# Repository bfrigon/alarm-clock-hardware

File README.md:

alarm-clock
===========

Project page at http://www.bfrigon.com/posts/projects/alarm-clock

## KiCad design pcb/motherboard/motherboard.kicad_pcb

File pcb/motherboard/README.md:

### Motherboard ###

```
Part #  : CLK-PC-03
REV.    : A
```

#### Documents ####

* [Schematic (PDF)](https://raw.githubusercontent.com/bfrigon/project-alarm-clock/master/drawings/schematics/clk-sch-03.pdf)
* [Bill of material](/pcb/motherboard/bom/bom.md)

#### 3D render ####

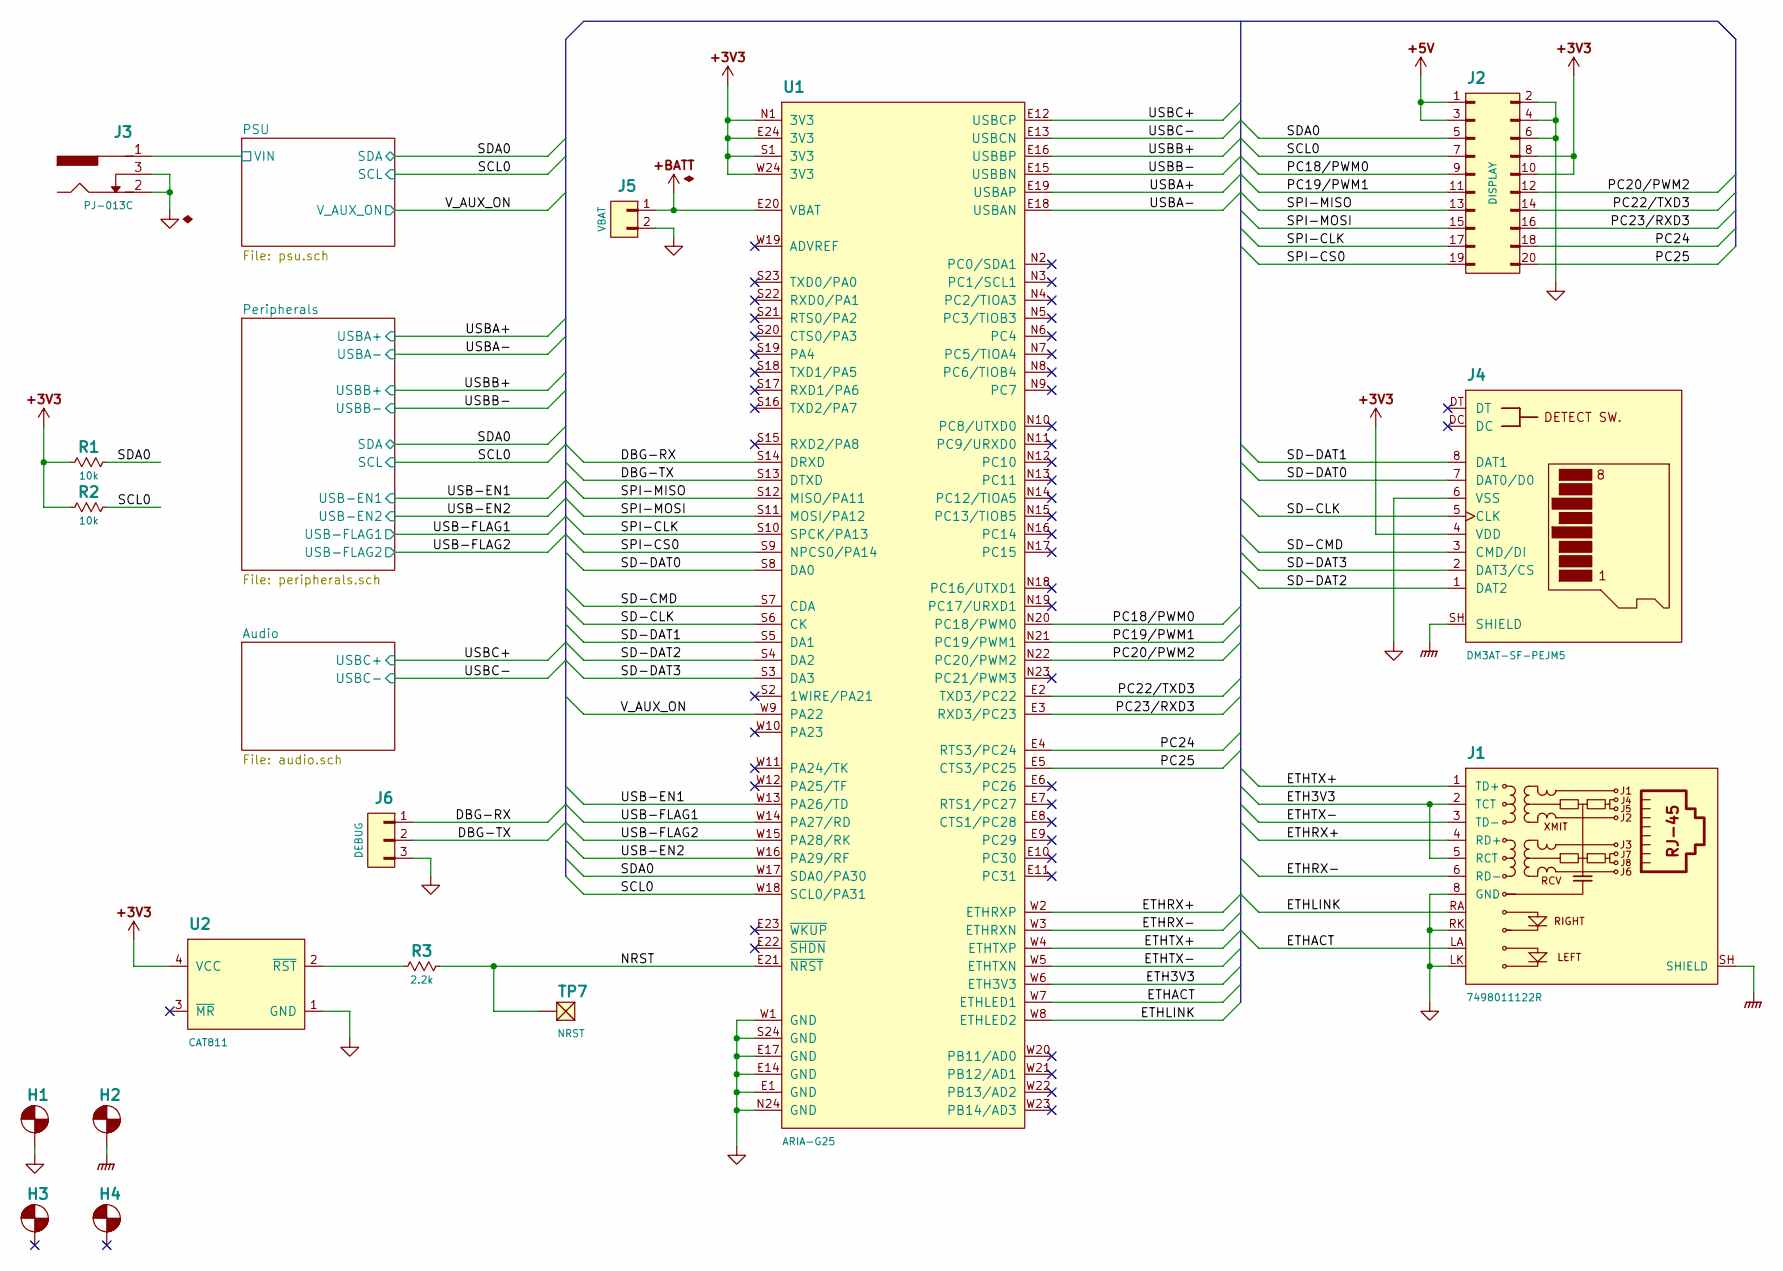
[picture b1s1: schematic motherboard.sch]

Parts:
H1, H2, H3, H4: Hole; Hole-Screw-#4
J1: 7498011122R; RJ45-WURTH-7498011122R
J2: DISPLAY; DF13A-20DP-1.25
J3: PJ-013C; CUI-PJ-031CH
J4: DM3AT-SF-PEJM5; HIROSE-MICROSD-DM3AT-SF
J5: VBAT; WP-75mil-1x02
J6: DEBUG; DF3DZ-3P-2VXX
R1, R2: 10k; R-0603
R3: 2.2k; R-0603
TP7: NRST; TEST-POINT-50
U1: ARIA-G25
U2: CAT811; SOT-143

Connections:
+BATT: J5.1, U1.E20 (VBAT)
/Audio/USBC+: U1.E12 (USBCP); also elsewhere on the board
/Audio/USBC-: U1.E13 (USBCN); also elsewhere on the board
/DBG-RX: J6.1, U1.S14 (DRXD)
/DBG-TX: J6.2, U1.S13 (DTXD)
/ETH3V3: J1.2 (TCT), J1.5 (RCT), U1.W6 (ETH3V3)
/ETHACT: J1.LA, U1.W7 (ETHLED1)
/ETHLINK: J1.RA, U1.W8 (ETHLED2)
/ETHRX+: J1.4 (RD+), U1.W2 (ETHRXP)
/ETHRX-: J1.6 (RD-), U1.W3 (ETHRXN)
/ETHTX+: J1.1 (TD+), U1.W4 (ETHTXP)
/ETHTX-: J1.3 (TD-), U1.W5 (ETHTXN)
/NRST: R3.2, TP7.1, U1.E21 (~NRST)
/PC18/PWM0: J2.9, U1.N20 (PC18/PWM0)
/PC19/PWM1: J2.11, U1.N21 (PC19/PWM1)
/PC20/PWM2: J2.12, U1.N22 (PC20/PWM2)
/PC22/TXD3: J2.14, U1.E2 (TXD3/PC22)
/PC23/RXD3: J2.16, U1.E3 (RXD3/PC23)
/PC24: J2.18, U1.E4 (RTS3/PC24)
/PC25: J2.20, U1.E5 (CTS3/PC25)
/PSU/SCL: J2.7, R2.2, U1.W18 (SCL0/PA31); also elsewhere on the board
/PSU/SDA: J2.5, R1.2, U1.W17 (SDA0/PA30); also elsewhere on the board
/PSU/VIN: J3.1; also elsewhere on the board
/PSU/V_AUX_ON: U1.W9 (PA22); also elsewhere on the board
/Peripherals/USB-EN1: U1.W13 (PA26/TD); also elsewhere on the board
/Peripherals/USB-EN2: U1.W16 (PA29/RF); also elsewhere on the board
/Peripherals/USB-FLAG1: U1.W14 (PA27/RD); also elsewhere on the board
/Peripherals/USB-FLAG2: U1.W15 (PA28/RK); also elsewhere on the board
/Peripherals/USBA+: U1.E19 (USBAP); also elsewhere on the board
/Peripherals/USBA-: U1.E18 (USBAN); also elsewhere on the board
/Peripherals/USBB+: U1.E16 (USBBP); also elsewhere on the board
/Peripherals/USBB-: U1.E15 (USBBN); also elsewhere on the board
/SD-CLK: J4.5 (CLK), U1.S6 (CK)
/SD-CMD: J4.3 (CMD/DI), U1.S7 (CDA)
/SD-DAT0: J4.7 (DAT0/D0), U1.S8 (DA0)
/SD-DAT1: J4.8 (DAT1), U1.S5 (DA1)
/SD-DAT2: J4.1 (DAT2), U1.S4 (DA2)
/SD-DAT3: J4.2 (DAT3/CS), U1.S3 (DA3)
/SPI-CLK: J2.17, U1.S10 (SPCK/PA13)
/SPI-CS0: J2.19, U1.S9 (NPCS0/PA14)
/SPI-MISO: J2.13, U1.S12 (MISO/PA11)
/SPI-MOSI: J2.15, U1.S11 (MOSI/PA12)
unnamed: R3.1, U2.2 (~RST)

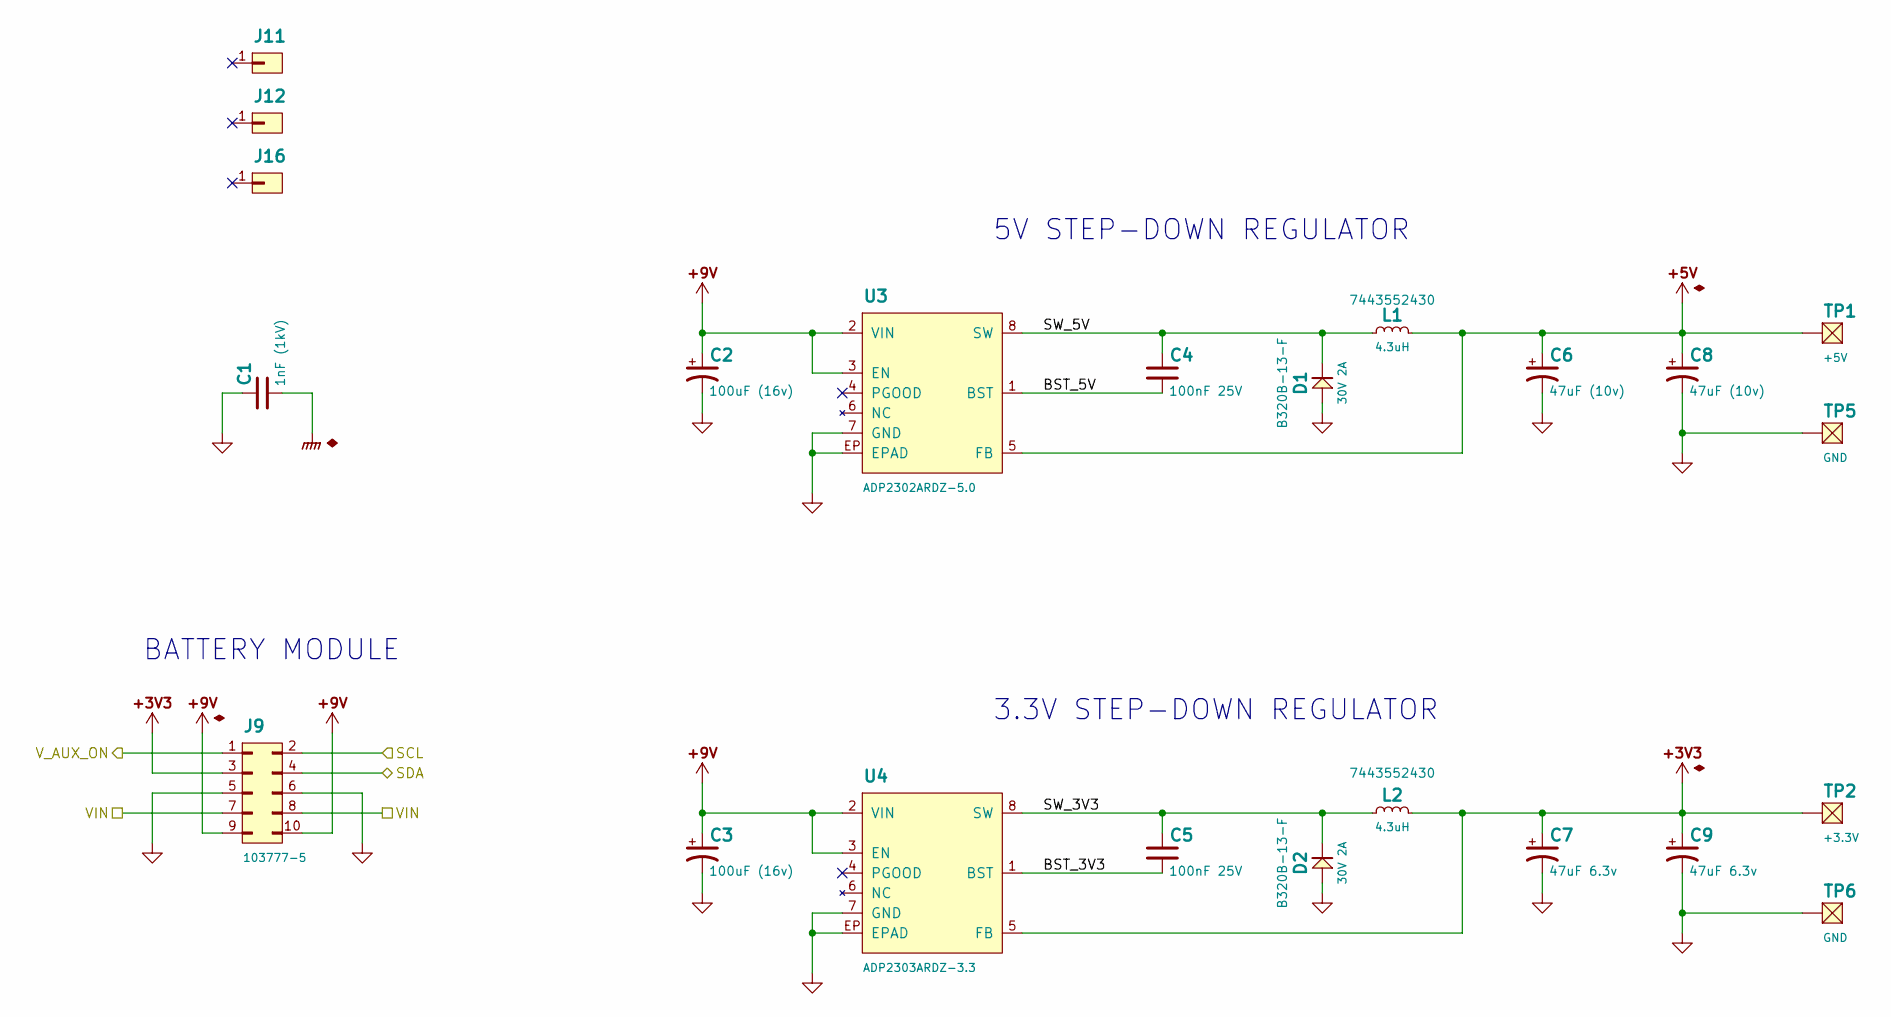
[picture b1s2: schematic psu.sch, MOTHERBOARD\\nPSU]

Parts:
C1: 1nF (1kV); C-0805
C2, C3: 100uF (16v); CPL-1210; Part EMK325ABJ107MM-T
C4, C5: 100nF 25V; C-0603
C6, C8: 47uF (10v); CPL-1206; Part LMK316BJ476ML-T
C7: 47uF 6.3v; CPL-1206; Part GRM31CR60J476ME19K
C9: 47uF 6.3v; CPL-1206; Part# GRM31CR60J476ME19K
D1: 30V 2A; DO-214-AA; PART B320B-13-F
D2: 30V 2A; DO-214-AA; Part B320B-13-F
J9: 103777-5; HDR-M-2x05
J11, J12, J16: 103741-1; HDR-M-1x01
L1, L2: 4.3uH; IND-10X10; PART 7443552430
TP1: +5V; TEST-POINT-50
TP2: +3.3V; TEST-POINT-50
TP5, TP6: GND; TEST-POINT-50
U3: ADP2302ARDZ-5.0; 8-EP
U4: ADP2303ARDZ-3.3; 8-EP

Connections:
/PSU/BST_3V3: C5.1, U4.1 (BST)
/PSU/BST_5V: C4.1, U3.1 (BST)
/PSU/SCL: J9.2; also elsewhere on the board
/PSU/SDA: J9.4; also elsewhere on the board
/PSU/SW_3V3: C5.2, D2.K, L2.1, U4.8 (SW)
/PSU/SW_5V: C4.2, D1.K, L1.1, U3.8 (SW)
/PSU/VIN: J9.7, J9.8; also elsewhere on the board
/PSU/V_AUX_ON: J9.1; also elsewhere on the board

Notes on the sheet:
5V STEP-DOWN REGULATOR
3.3V STEP-DOWN REGULATOR
BATTERY MODULE

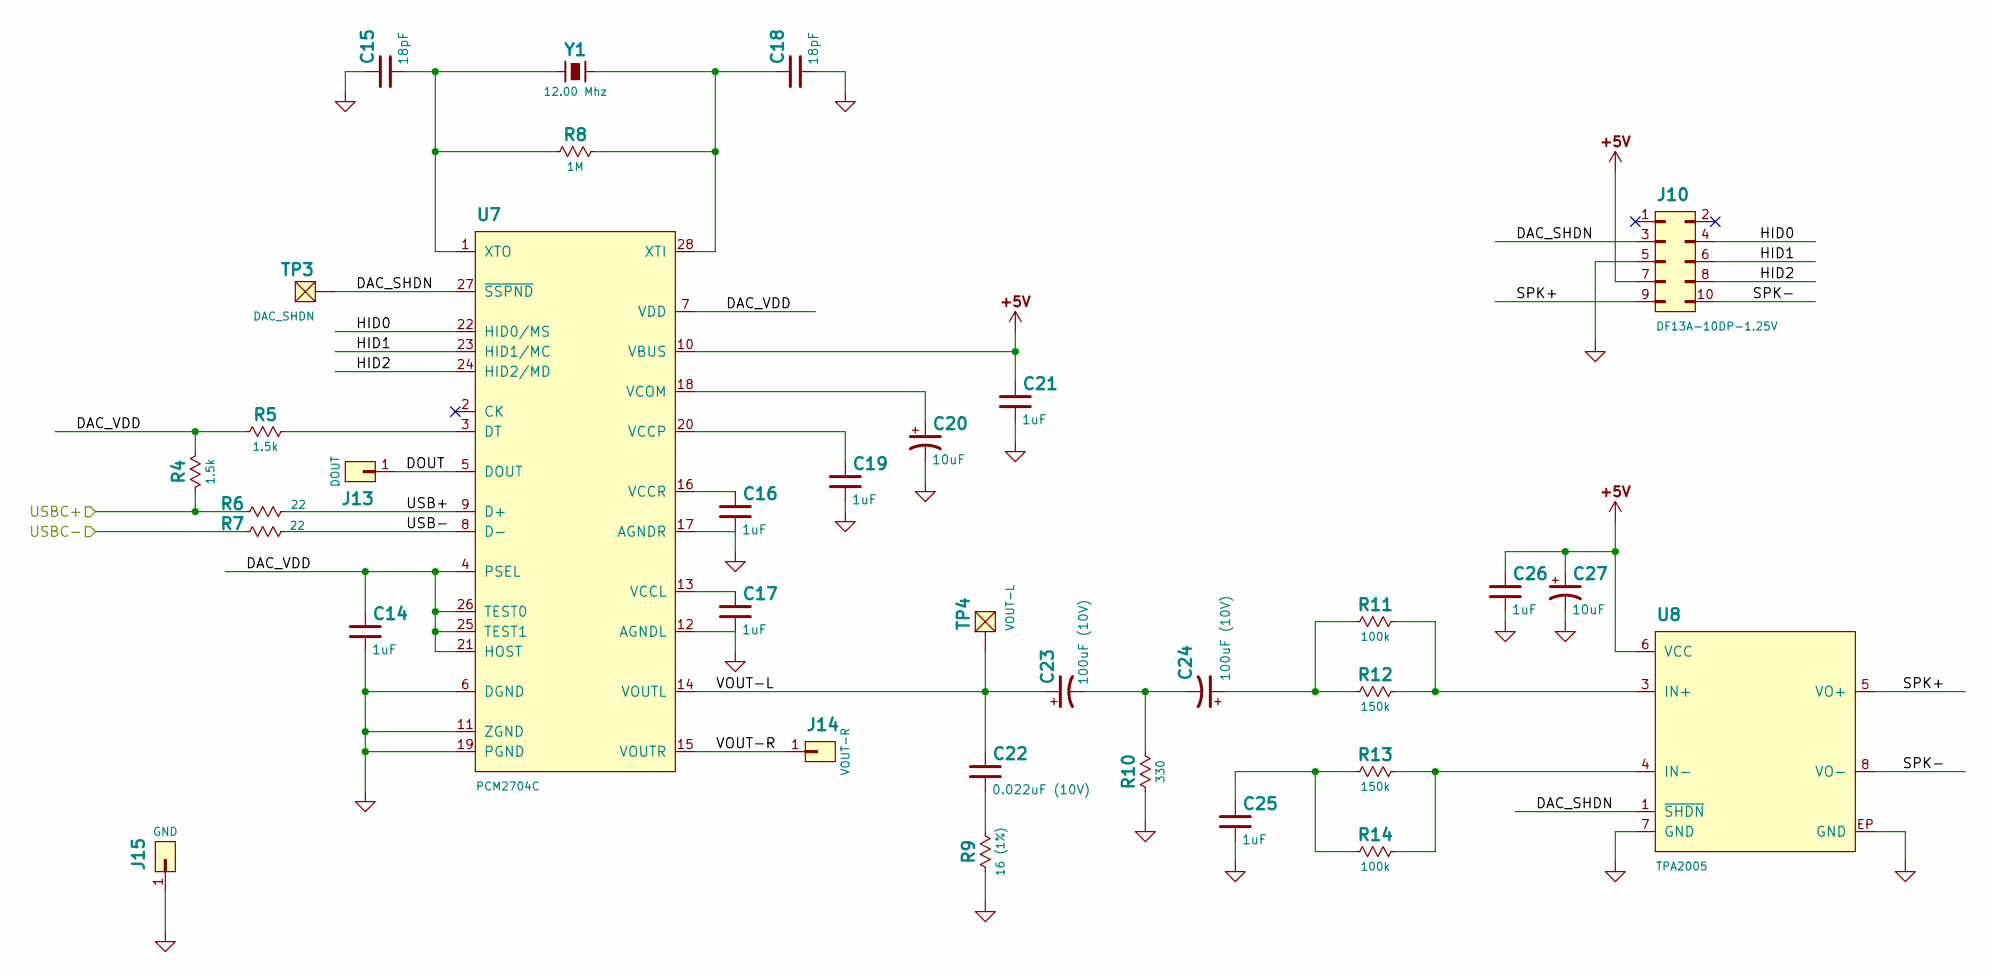
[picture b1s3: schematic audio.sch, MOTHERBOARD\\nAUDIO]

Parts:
C14, C16, C17, C19, C21, C25, C26: 1uF; C-0603
C15, C18: 18pF; C-0603
C20, C27: 10uF; CPL-0805
C22: 0.022uF (10V); C-0603
C23: 100uF (10V); CPL-1210
C24: 100uF (10V); CPL-0805
J10: DF13A-10DP-1.25V; DF13A-10DP-1.25
J13: DOUT; WP-50mil-1x01
J14: VOUT-R; WP-50mil-1x01
J15: GND; WP-50mil-1x01
R4, R5: 1.5k; R-0603
R6, R7: 22; R-0603
R8: 1M; R-0603
R9: 16 (1%); R-0603
R10: 330; R-0603
R11, R14: 100k; R-0603
R12, R13: 150k; R-0603
TP3: DAC_SHDN; TEST-POINT-50
TP4: VOUT-L; TEST-POINT-50
U7: PCM2704C; SSOP28
U8: TPA2005; PPSOP8
Y1: 12.00 Mhz; HC49UP

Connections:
/Audio/DAC_SHDN: J10.3, TP3.1, U7.27 (~SSPND), U8.1 (~SHDN)
/Audio/DAC_VDD: C14.2, R4.1, R5.1, U7.4 (PSEL), U7.7 (VDD), U7.21 (HOST), U7.25 (TEST1), U7.26 (TEST0)
/Audio/DOUT: J13.1, U7.5 (DOUT)
/Audio/HID0: J10.4, U7.22 (HID0/MS)
/Audio/HID1: J10.6, U7.23 (HID1/MC)
/Audio/HID2: J10.8, U7.24 (HID2/MD)
/Audio/SPK+: J10.9, U8.5 (VO+)
/Audio/SPK-: J10.10, U8.8 (VO-)
/Audio/USB+: R6.2, U7.9 (D+)
/Audio/USB-: R7.2, U7.8 (D-)
/Audio/USBC+: R4.2, R6.1; also elsewhere on the board
/Audio/USBC-: R7.1; also elsewhere on the board
/Audio/VOUT-L: C22.2, C23.A, TP4.1, U7.14 (VOUTL)
/Audio/VOUT-R: J14.1, U7.15 (VOUTR)
unnamed: C15.1, R8.1, U7.1 (XTO), Y1.1
unnamed: C16.2, U7.16 (VCCR)
unnamed: C17.2, U7.13 (VCCL)
unnamed: C18.2, R8.2, U7.28 (XTI), Y1.2
unnamed: C19.2, U7.20 (VCCP)
unnamed: C20.A, U7.18 (VCOM)
unnamed: C22.1, R9.2
unnamed: C23.K, C24.K, R10.2
unnamed: C24.A, R11.1, R12.1
unnamed: C25.2, R13.1, R14.1
unnamed: R5.2, U7.3 (DT)
unnamed: R11.2, R12.2, U8.3 (IN+)
unnamed: R13.2, R14.2, U8.4 (IN-)

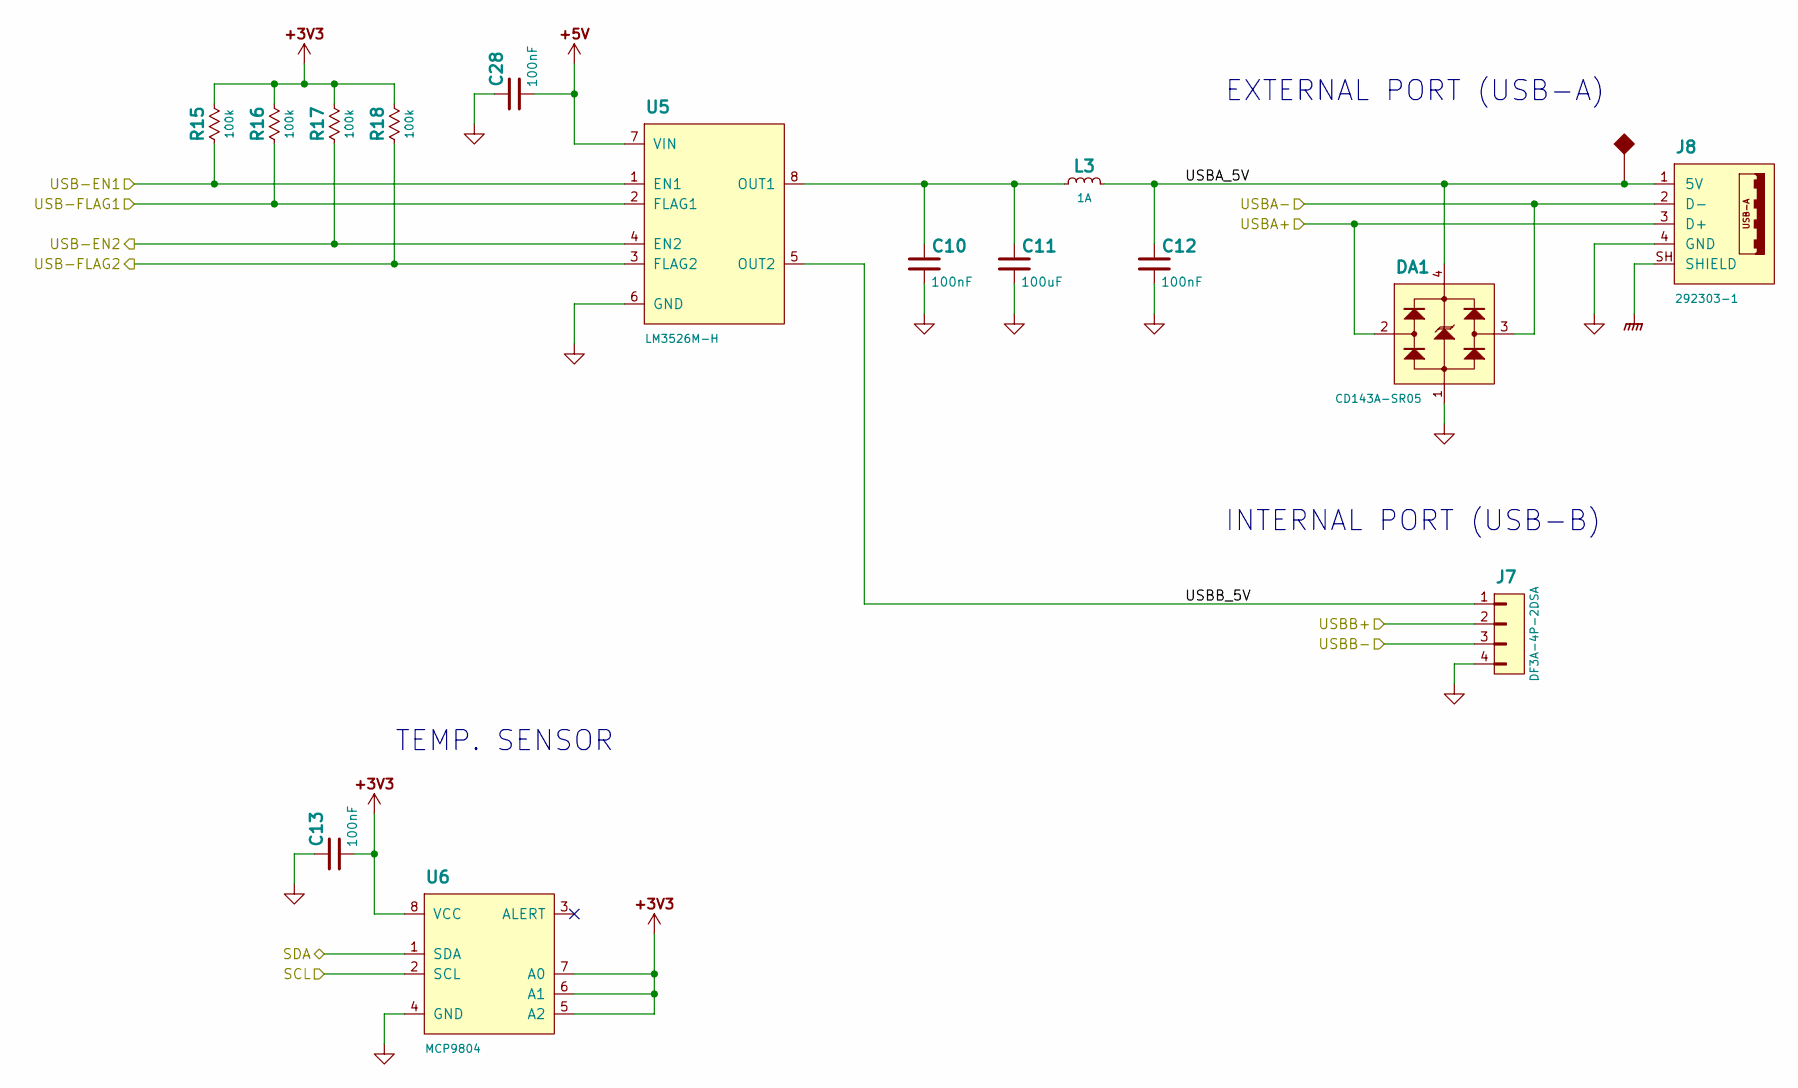
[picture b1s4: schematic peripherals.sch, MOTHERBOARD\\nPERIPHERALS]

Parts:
C10, C12, C13, C28: 100nF; C-0603
C11: 100uF; C-0805
DA1: CD143A-SR05; SOT-143
J7: DF3A-4P-2DSA
J8: 292303-1; USBA-TE-292303-1
L3: 1A; FER-0805
R15, R16, R17, R18: 100k; R-0603
U5: LM3526M-H; 8
U6: MCP9804; MSOP8

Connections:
/PSU/SCL: U6.2 (SCL); also elsewhere on the board
/PSU/SDA: U6.1 (SDA); also elsewhere on the board
/Peripherals/USB-EN1: R15.1, U5.1 (EN1); also elsewhere on the board
/Peripherals/USB-EN2: R17.1, U5.4 (EN2); also elsewhere on the board
/Peripherals/USB-FLAG1: R16.1, U5.2 (FLAG1); also elsewhere on the board
/Peripherals/USB-FLAG2: R18.1, U5.3 (FLAG2); also elsewhere on the board
/Peripherals/USBA+: DA1.2, J8.3 (D+); also elsewhere on the board
/Peripherals/USBA-: DA1.3, J8.2 (D-); also elsewhere on the board
/Peripherals/USBA_5V: C12.2, DA1.4, J8.1 (5V), L3.2
/Peripherals/USBB+: J7.2; also elsewhere on the board
/Peripherals/USBB-: J7.3; also elsewhere on the board
/Peripherals/USBB_5V: J7.1, U5.5 (OUT2)
unnamed: C10.2, C11.2, L3.1, U5.8 (OUT1)

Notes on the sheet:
INTERNAL PORT (USB-B)
EXTERNAL PORT (USB-A)
TEMP. SENSOR

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
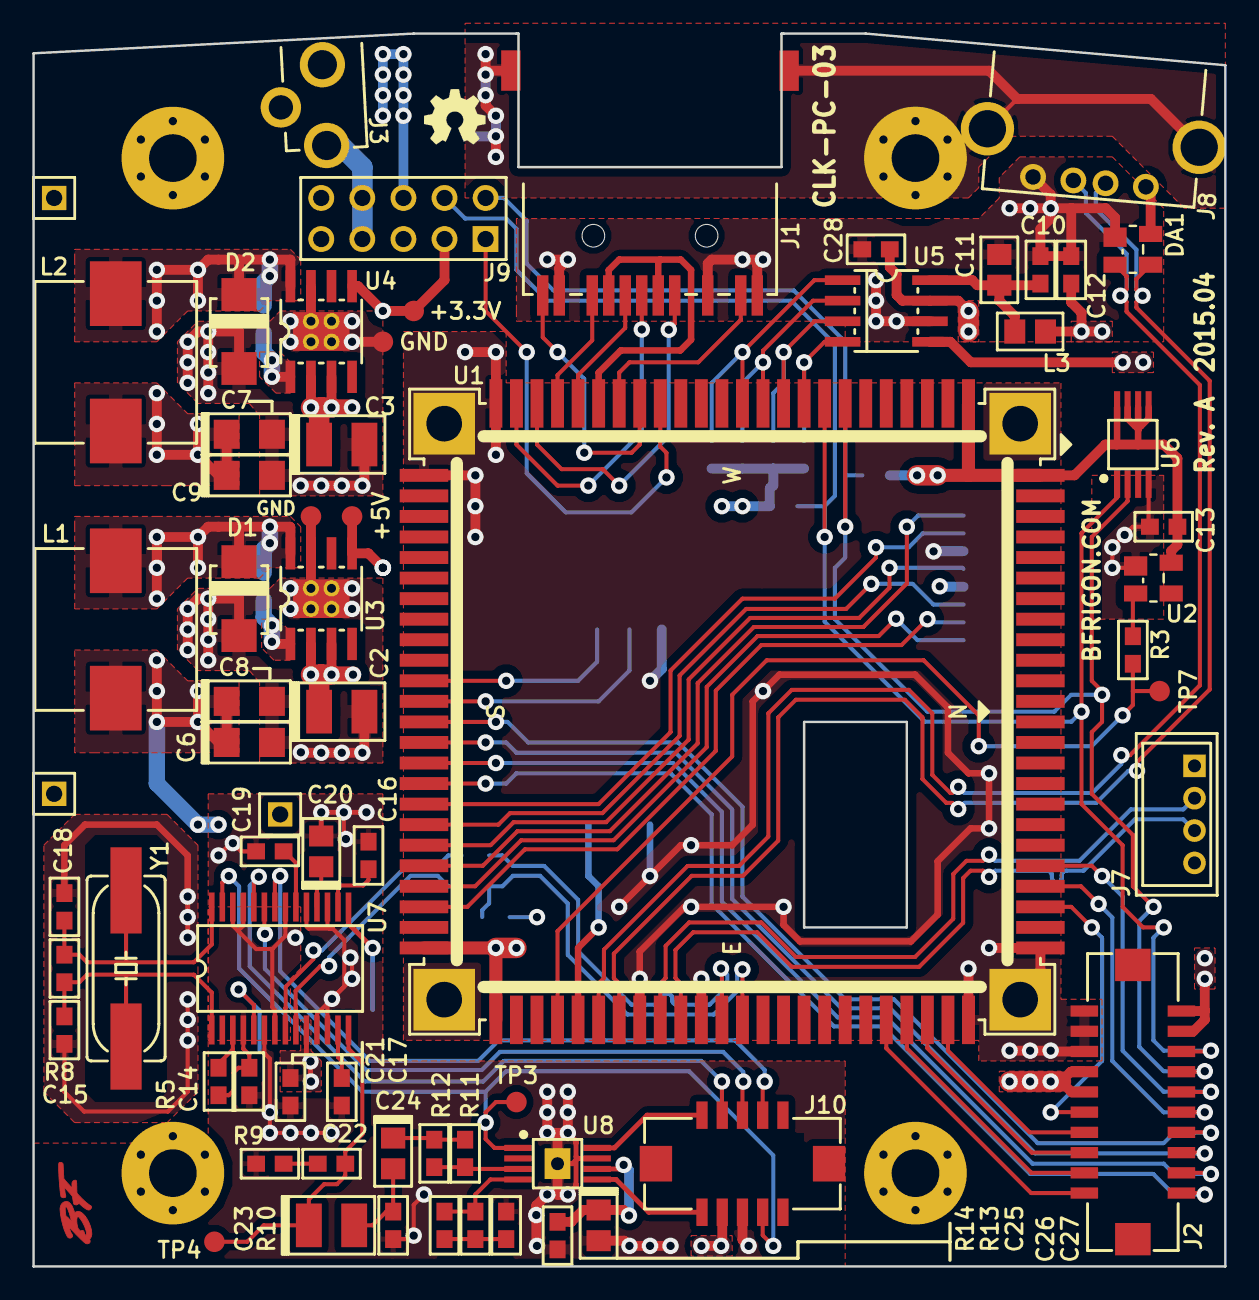
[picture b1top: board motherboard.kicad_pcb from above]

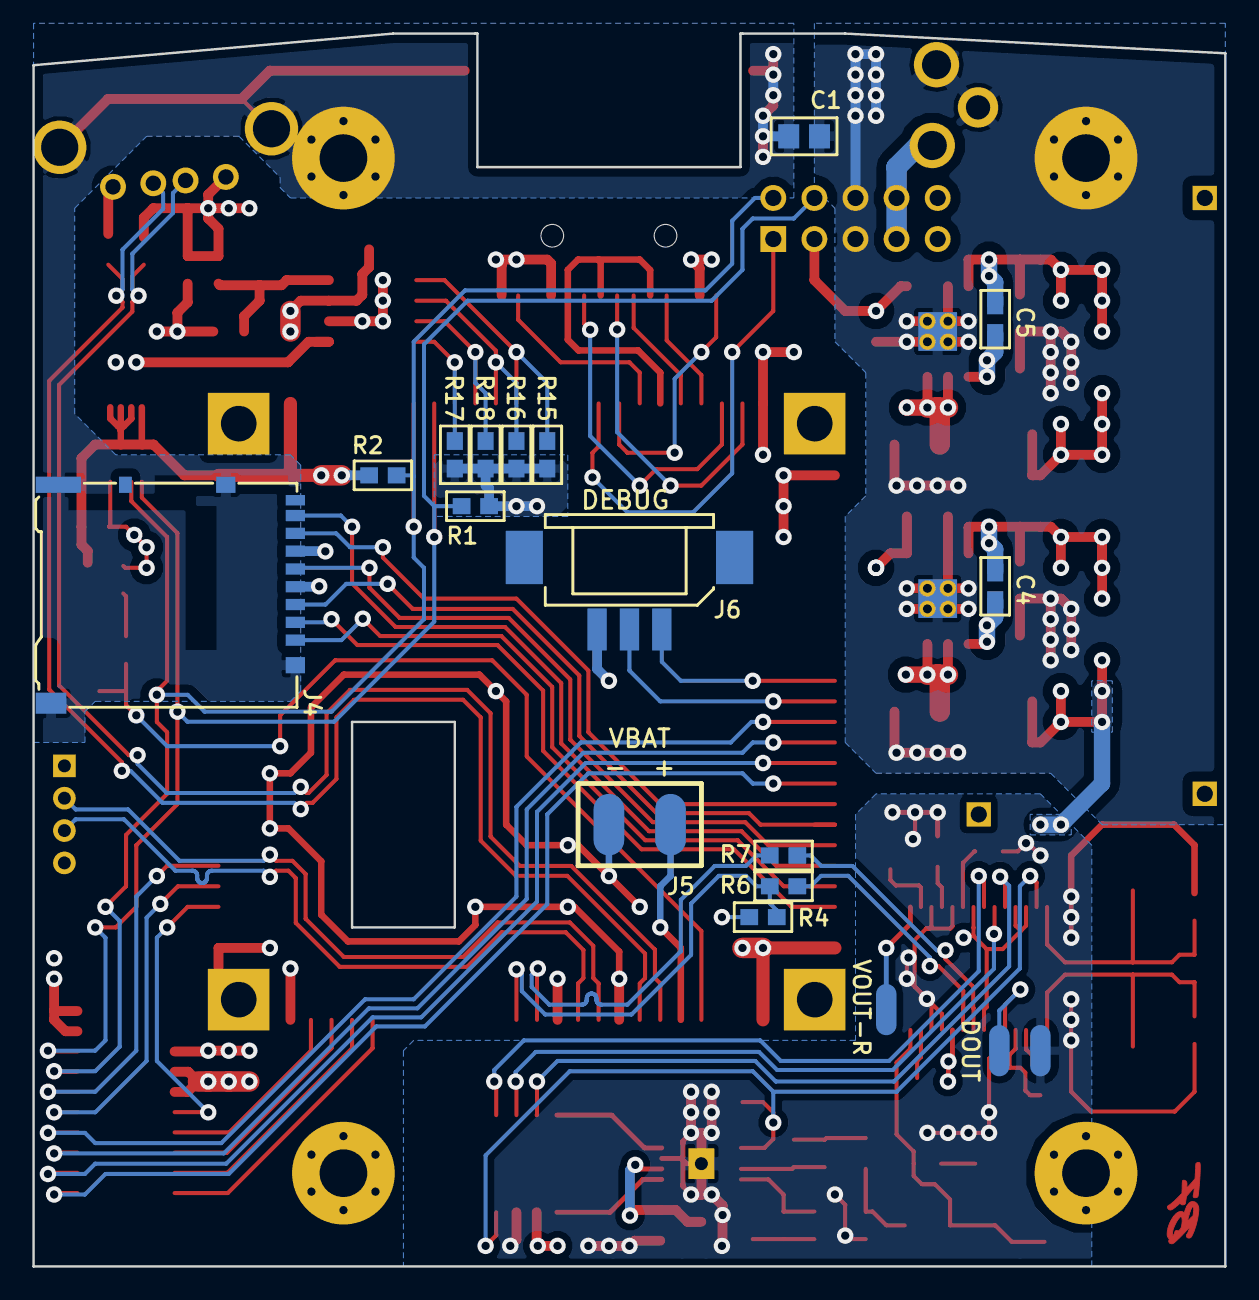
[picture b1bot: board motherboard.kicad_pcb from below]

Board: 4 copper layers, 73.7 x 76.2 mm, 89 parts (18 on the bottom side), 80 nets.

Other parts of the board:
LOGO-OSHW-150: OSHW; LOGO-OSHW-150

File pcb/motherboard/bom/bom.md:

### Bill of material ###

```
Date    : Sun 12 Apr 2015
Doc. ID : CLK-SCH-03
Project : Alarm Clock
Title   : Motherboard

Part #  : CLK-PC-03
REV.    : A

Components : 73
```

------------------------------------------------------------------------------------------------------------------------


| Qty | Ref.                            | Description                                   | Value         | Part #               | Footprint               |
|-----|---------------------------------|-----------------------------------------------|---------------|----------------------|-------------------------|
| 3   | J11-J12, J16                    | Header - Single Row - 1 Pos                   | -             | 103741-1             | HDR-M-1x01              |
| 1   | J9                              | Header - Dual Row - 10 Pos                    | -             | 103777-5             | HDR-M-2x05              |
| 1   | J8                              | USB Connector - Type A                        | -             | 292303-1             | USBA-TE-292303-1        |
| 1   | J1                              | RJ45 Connector with magnetics and leds        | -             | 7498011122R          | RJ45-WURTH-7498011122R  |
| 1   | J10                             | Header - Dual Row - 10 Pos                    | -             | DF13A-10DP-1.25V     | DF13A-10DP-1.25         |
| 1   | J2                              | Header - Dual Row - 20 Pos                    | -             | DF13A-20DP-1.25V(25) | DF13A-20DP-1.25         |
| 1   | J7                              | Header - Single Row - 4 Pos                   | -             | DF3A-4P-2DSA         | DF3A-4P-2DSA            |
| 1   | J6                              | Header - Single Row - 3 Pos                   | -             | DF3DZ-3P-2V21        | DF3DZ-3P-2VXX           |
| 1   | J4                              | Micro SD card connector                       | -             | DM3AT-SF-PEJM5       | HIROSE-MICROSD-DM3AT-SF |
| 1   | J3                              | DC Barrel Jack                                | -             | PJ-013C              | CUI-PJ-031CH            |
| 1   | U3                              | 2A Step-down regulator                        | -             | ADP2302ARDZ-5.0      | SOIC-8-EP               |
| 1   | U4                              | 3A Step-down regulator                        | -             | ADP2303ARDZ-3.3      | SOIC-8-EP               |
| 1   | U1                              | AT91SAM9G25 SoM                               | -             | ARIA-G25             | Misc:ARIA-G25           |
| 1   | U2                              | 4-Pin Microprocessor Power Supply Supervisors | -             | CAT811TTBI-T3        | SOT-143                 |
| 1   | U5                              | Dual port USB power switch with OC protection | -             | LM3526M-H            | SOIC-8                  |
| 1   | U6                              | Digital Temperature Sensor                    | -             | MCP9804              | MSOP8                   |
| 1   | U7                              | Stereo Audio DAC with USB Interface           | -             | PCM2704C             | SSOP28                  |
| 1   | U8                              | 1.4W Mono Class-D Audio Amplifier             | -             | TPA2005              | PPSOP8                  |
| 1   | C22                             | capacitor                                     | 0.022uF (10V) | -                    | SMT-0603                |
| 2   | R4-R5                           | Resistor                                      | 1.5k          | -                    | SMT-0603                |
| 6   | R11, R14-R18                    | Resistor                                      | 100k          | -                    | SMT-0603                |
| 2   | C4-C5                           | capacitor                                     | 100nF 25V     | -                    | SMT-0603                |
| 4   | C10, C12-C13, C28               | capacitor                                     | 100nF         | -                    | SMT-0603                |
| 1   | C23                             | Electrolytic capacitor                        | 100uF (10V)   | -                    | SMT-1210                |
| 1   | C11                             | capacitor                                     | 100uF         | -                    | SMT-0805                |
| 2   | R1-R2                           | Resistor                                      | 10k           | -                    | SMT-0603                |
| 2   | C20, C27                        | Electrolytic capacitor                        | 10uF          | -                    | SMT-0805                |
| 1   | Y1                              | Crystal                                       | 12.00 Mhz     | -                    | HC49UP                  |
| 2   | R12-R13                         | Resistor                                      | 150k          | -                    | SMT-0603                |
| 1   | R9                              | Resistor                                      | 16 (1%)       | -                    | SMT-0603                |
| 2   | C15, C18                        | capacitor                                     | 18pF          | -                    | SMT-0603                |
| 1   | L3                              | Inductor                                      | 1A            | -                    | SMT-0805                |
| 1   | R8                              | Resistor                                      | 1M            | -                    | SMT-0603                |
| 1   | C1                              | capacitor                                     | 1nF (1kV)     | -                    | SMT-0805                |
| 1   | C24                             | Electrolytic capacitor                        | 1uF (10V)     | -                    | SMT-0805                |
| 7   | C14, C16-C17, C19, C21, C25-C26 | capacitor                                     | 1uF           | -                    | SMT-0603                |
| 1   | R3                              | Resistor                                      | 2.2k          | -                    | SMT-0603                |
| 2   | R6-R7                           | Resistor                                      | 22            | -                    | SMT-0603                |
| 1   | R10                             | Resistor                                      | 330           | -                    | SMT-0603                |
| 1   | DA1                             | TVS Diode Array                               | CD143A-SR05   | -                    | SOT-143                 |
| 2   | L1-L2                           | Inductor                                      | 4.3uH         | 7443552430           | SMT:IND-10X10           |
| 2   | D1-D2                           | Diode                                         | 30V 2A        | B320B-13-F           | SMT:DO-214-AA           |
| 2   | C2-C3                           | Electrolytic capacitor                        | 100uF (16v)   | EMK325ABJ107MM-T     | SMT-1210                |
| 2   | C7, C9                          | Electrolytic capacitor                        | 47uF (6.3v)   | GRM31CR60J476ME19K   | SMT-1206                |
| 2   | C6, C8                          | Electrolytic capacitor                        | 47uF (10v)    | LMK316BJ476ML-T      | SMT-1206                |

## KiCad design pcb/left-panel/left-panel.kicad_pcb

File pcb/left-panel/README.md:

### Left panel ###

```
Part #  : CLK-PC-04
REV.    : A
```

#### Documents ####

* [Schematic (PDF)](https://raw.githubusercontent.com/bfrigon/project-alarm-clock/master/drawings/schematics/clk-sch-04.pdf)
* [Bill of material](/pcb/left-panel/bom/bom.md)

#### 3D render ####

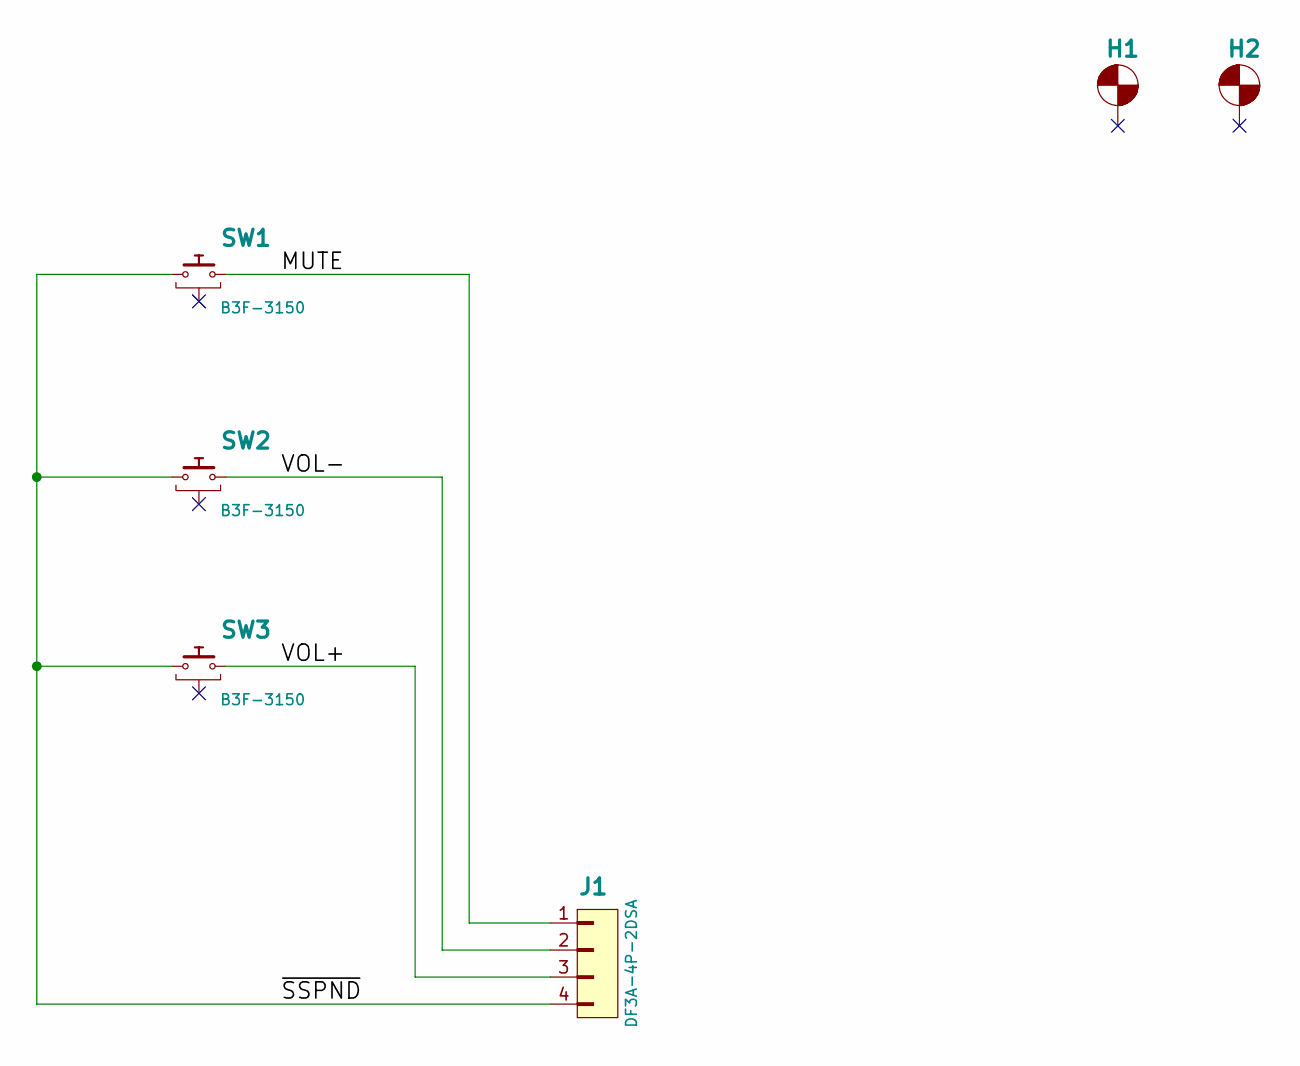
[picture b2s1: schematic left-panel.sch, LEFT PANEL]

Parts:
H1, H2: Hole; Hole-Screw-NP-#4
J1: DF3A-4P-2DSA
SW1, SW2, SW3: B3F-3150; B3F-315X

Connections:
/MUTE: J1.1, SW1.2
/VOL+: J1.3, SW3.2
/VOL-: J1.2, SW2.2
/~SSPND: J1.4, SW1.1, SW2.1, SW3.1

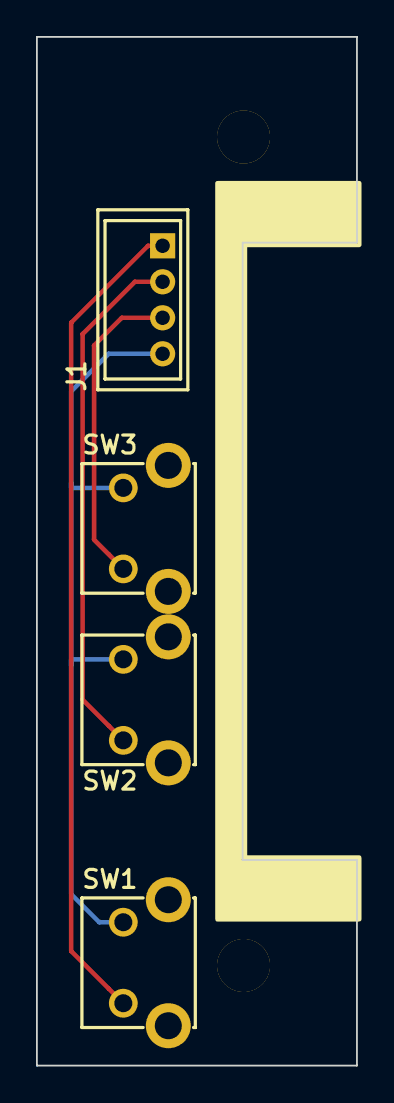
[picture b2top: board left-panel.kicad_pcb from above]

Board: 2 copper layers, 17.8 x 57.2 mm, 6 parts (0 on the bottom side), 4 nets.

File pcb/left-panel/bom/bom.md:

### Bill of material ###

```
Date    : Thu 19 Mar 2015
Doc. ID : CLK-SCH-04
Project : Alarm Clock
Title   : Left Panel

Part #  : CLK-PC-04
REV.    : A

Components : 4
```

------------------------------------------------------------------------------------------------------------------------


| Qty | Ref.    | Description                            | Value | Part #       | Footprint         |
|-----|---------|----------------------------------------|-------|--------------|-------------------|
| 1   | J1      | Header - Single Row - 4 Pos            | -     | DF3A-4P-2DSA | DF3A-4P-2DSA      |
| 3   | SW1-SW3 | Momentary SPST switch with ground tabs | -     | B3F-3150     | Switches:B3F-315X |

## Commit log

2014-09-07 Added decoupling caps
2014-09-09 Cleaned up project tree
2014-09-18 Added Model B drawings
2014-10-19 Corrected drawings of touch panel PCB
2014-10-23 Overlay design
2014-10-28 Changed files for laser cutting to DXF instead of SVG
2014-12-29 Display base pcb (rev C), Touch panel (rev B)
2015-01-04 Changed page format on schematics to US letter (8.5" x 11")
2015-01-04 Moved notes to docs folder
2015-01-05 Updated mechanical drawings for model B
2015-01-06 3D render for model B
2015-01-06 BOM for audio test board
2015-01-07 Updated overlay to reflect the changes on touch pcb (rev B)
2015-01-09 Added marks for cutting
2015-01-09 Updated drawings to reflect changes on touch keypad PCB (leds on snooze, time and alarm button)
2015-01-22 at42qt1085 tests
2015-01-25 Added a temperature sensor IC (U9) to controller PCB
2015-01-25 Changed file format to .md for notes
2015-01-25 Corrected markdown syntax on notes
2015-01-29 Script to sets the correct title of each drawings and generate a TOC for the clk-dwg.pdf
2015-01-29 Updated design files
2015-02-08 Added battery interface PCB drawings (PC-08, DWG-12)
2015-02-08 modified dimensions of left panel PCB to fit speaker holder
2015-02-08 Modified fonts of title block on all drawings
2015-02-08 Added description to each Eagle project directories
2015-02-08 Created skeleton for PC-08 : Battery interface
2015-02-09 Fixed dimensions error in CLK-DWG-05 (Left panel PCB)
2015-02-11 Swapped USBC and USBB, USBC will be used for the PCM2704
2015-02-12 Fixed dimensions error in PC-04 (Left panel PCB)
2015-02-12 Switched motherboard (PC-03) to 4 layers design
2015-03-19 Converted motherboard and left-panel project files to Kicad
2015-03-21 Updated drawings for clk-pc-03
2015-04-06 Changed crystal location for PCM2704
2015-04-06 Added worksheet for left-panel
2015-04-12 Added bill of material for CLK-PC-03
2015-04-12 Tidy up motherboard schematic
2015-04-12 Added BOM for CLK-PC-04
2015-04-12 Updated schematic for CLK-PC-04
2015-04-12 Added components count on CLK-PC-03 BOM
2015-04-12 Added 3D views of PC-03 and PC04
2015-04-12 Create README.md file for CLK-PC-03
2015-04-12 Fixed incorrect sheet size for CLK-SCH-03 (Motherboard)
2015-04-12 Add gerber files
2015-04-12 Add README.md for PC-04
2015-04-12 Added gerber files for PC-04 (Left panel)
2015-04-12 Converted PC-08 (Battery interface) project files to Kicad
2015-04-12 Updated drawing for PC-08 (Battery interface)
2015-04-14 Added Debug connector in drawings
2015-04-14 Fixed wrong cap value for C24 and part # for C7,C9
2015-04-22 Incresed height of display epoxy casting by 1/16 inch
2015-04-22 Only modify pdf metadata for files that were modified
2015-05-03 Wrong polarity on battery connector label
